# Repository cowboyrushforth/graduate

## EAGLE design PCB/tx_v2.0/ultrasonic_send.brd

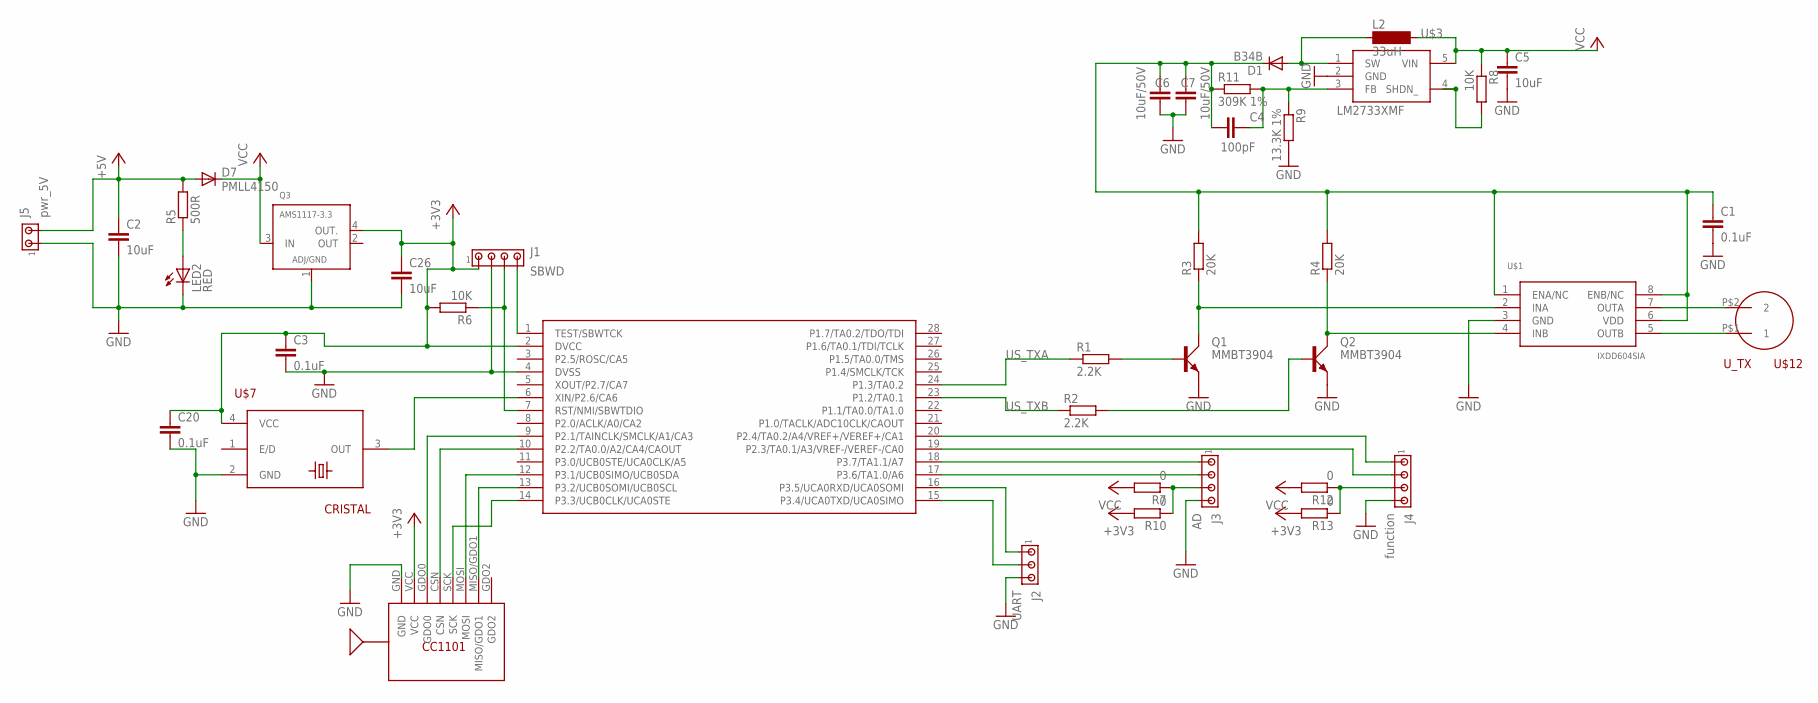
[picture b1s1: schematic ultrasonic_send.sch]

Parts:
C1, C3, C20: 0.1uF; C0805
C2, C5, C26: 10uF; C0805
C4: 100pF; C0805
C6, C7: 10uF/50V; C1210
D1: B34B; GF1
D7: PMLL4150; SOD80C
J1: SBWD; 10X04MTA
J2: UART; 10X03MTA
J3: AD; 10X04MTA
J4: function; 10X04MTA
J5: pwr_5V; 10X02MTA
L2: 33uH; MS85
LED2: RED; SML0805
Q1, Q2: MMBT3904; SOT23
Q3: AMS1117-3.3; SOT223-4
R1, R2: 2.2K; R0805
R3, R4: 20K; R0603
R5: 500R; R0603
R6, R8: 10K; R0603
R7, R10, R12, R13: 0; R0603
R9: 13.3K 1%; R0603
R11: 309K 1%; R0603
U$1: IXDD604SIA; SO8
U$2: MSP430F2112; PW_R-PDSO-G28
U$3: LM2733XMF; SOT23-DBV
U$4: CC1101
U$7: CRISTAL; CTS406
U$12: U_TX; ULTRASONIC

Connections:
+3V3: C3.1, C20.1, C26.1, J1.1, Q3.4 (OUT.), R6.2, R10.2, R13.2, U$2.2 (DVCC), U$4.VCC, U$7.4 (VCC)
+5V: C2.1, D7.A, J5.2, R5.2
GND: C1.2, C2.2, C3.2, C5.2, C6.2, C7.2, C20.2, C26.2, J1.2, J2.3, J3.4, J4.4, J5.1, LED2.C, Q1.2 (E), Q2.2 (E), Q3.1 (ADJ/GND), R9.2, U$1.3 (GND), U$2.4 (DVSS), U$3.2 (GND), U$4.GND, U$7.2 (GND)
unnamed: Q1.1 (B), R1.2
unnamed: Q2.1 (B), R2.2
unnamed: Q1.3 (C), R3.1, U$1.2 (INA)
unnamed: Q2.3 (C), R4.1, U$1.4 (INB)
unnamed: J1.4, U$2.1 (TEST/SBWTCK)
unnamed: LED2.A, R5.1
unnamed: U$2.6 (XIN/P2.6/CA6), U$7.3 (OUT)
unnamed: C1.1, C4.1, C6.1, C7.1, D1.C, R3.2, R4.2, R11.1, U$1.1 (ENA/NC), U$1.6 (VDD), U$1.8 (ENB/NC)
unnamed: J4.3, R12.1, R13.1
unnamed: J1.3, R6.1, U$2.7 (RST/NMI/SBWTDIO)
unnamed: U$2.9 (P2.1/TAINCLK/SMCLK/A1/CA3), U$4.GDO0
unnamed: U$2.10 (P2.2/TA0.0/A2/CA4/CAOUT), U$4.CSN
unnamed: U$2.12 (P3.1/UCB0SIMO/UCB0SDA), U$4.MOSI
unnamed: U$2.13 (P3.2/UCB0SOMI/UCB0SCL), U$4.MISO/GDO1
unnamed: U$2.14 (P3.3/UCB0CLK/UCA0STE), U$4.SCK
unnamed: J2.1, U$2.16 (P3.5/UCA0RXD/UCA0SOMI)
unnamed: J2.2, U$2.15 (P3.4/UCA0TXD/UCA0SIMO)
unnamed: J3.1, U$2.18 (P3.7/TA1.1/A7)
unnamed: J3.2, U$2.17 (P3.6/TA1.0/A6)
unnamed: J3.3, R7.1, R10.1
unnamed: R8.2, U$3.4 (SHDN_)
unnamed: D1.A, L2.1, U$3.1 (SW)
unnamed: C4.2, R9.1, R11.2, U$3.3 (FB)
unnamed: J4.1, U$2.20 (P2.4/TA0.2/A4/VREF+/VEREF+/CA1)
unnamed: U$1.7 (OUTA), U$12.P$2 (2)
unnamed: U$1.5 (OUTB), U$12.P$1 (1)
unnamed: J4.2, U$2.19 (P2.3/TA0.1/A3/VREF-/VEREF-/CA0)
OUT: Q3.2 (OUT)
US_TXA: R1.1, U$2.24 (P1.3/TA0.2)
US_TXB: R2.1, U$2.23 (P1.2/TA0.1)
VCC: C5.1, D7.C, L2.2, Q3.3 (IN), R7.2, R8.1, R12.2, U$3.5 (VIN)

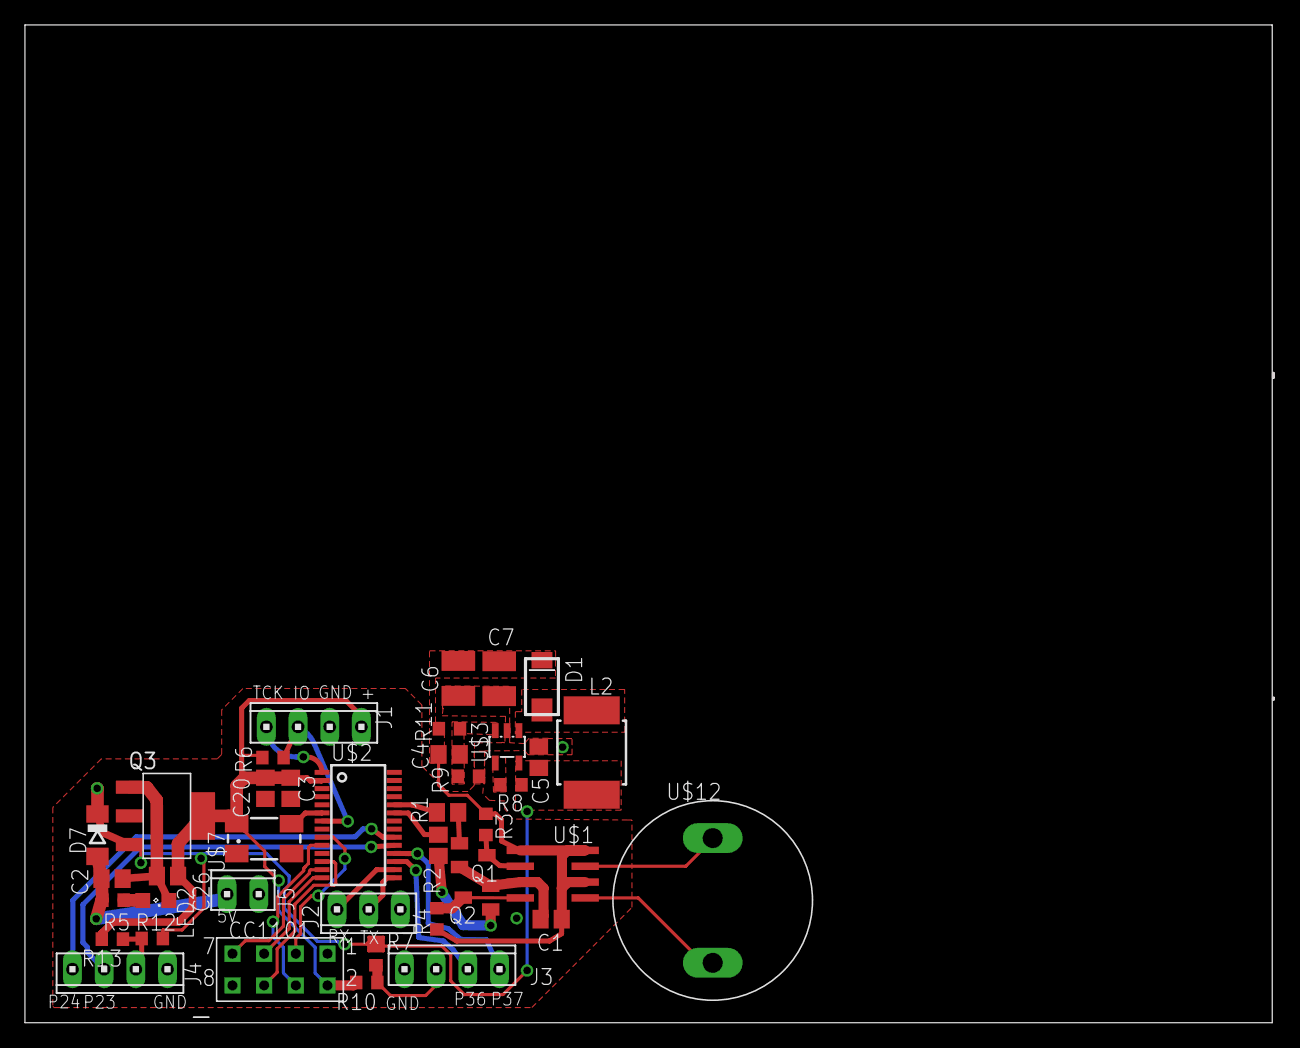
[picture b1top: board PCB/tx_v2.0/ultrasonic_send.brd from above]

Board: 2 copper layers, 100.0 x 79.7 mm, 40 parts (0 on the bottom side), 33 nets.

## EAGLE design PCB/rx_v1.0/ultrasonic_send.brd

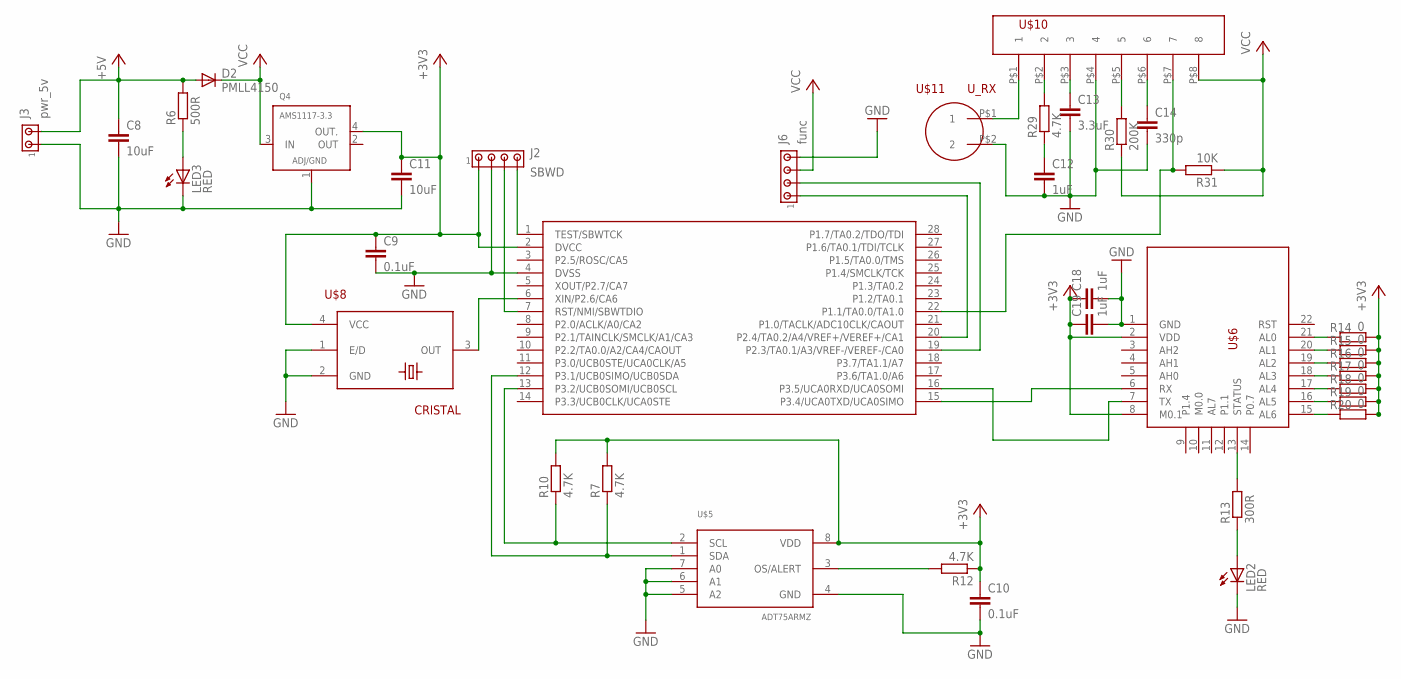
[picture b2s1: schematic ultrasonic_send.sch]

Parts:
C8, C11: 10uF; C0805
C9, C10: 0.1uF; C0805
C12, C18, C19: 1uF; C0805
C13: 3.3uF; C0805
C14: 330p; C0805
D2: PMLL4150; SOD80C
J2: SBWD; 10X04MTA
J3: pwr_5v; 10X02MTA
J6: func; 10X04MTA
LED2, LED3: RED; CHIP-LED0805
Q4: AMS1117-3.3; SOT223-4
R6: 500R; R0603
R7, R10, R12, R29: 4.7K; R0603
R13: 300R; R0603
R14, R15, R16, R17, R18, R19, R20: 0; R0603
R30: 200K; R0603
R31: 10K; R0603
U$4: MSP430F2112; PW_R-PDSO-G28
U$5: ADT75ARMZ; MSOP08
U$6: ZIGBEE
U$8: CRISTAL; CTS406
U$10: CX20106
U$11: U_RX; ULTRASONIC

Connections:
+3V3: C9.1, C10.1, C11.1, C18.1, C19.1, J2.1, Q4.4 (OUT.), R7.2, R10.2, R12.1, R14.1, R15.1, R16.1, R17.1, R18.1, R19.1, R20.1, U$4.2 (DVCC), U$5.8 (VDD), U$6.2 (VDD), U$6.8 (M0.1), U$8.4 (VCC)
+5V: C8.1, D2.A, J3.2, R6.2
GND: C8.2, C9.2, C10.2, C11.2, C12.2, C13.2, C14.2, C18.2, C19.2, J2.2, J3.1, J6.4, LED2.C, LED3.C, Q4.1 (ADJ/GND), U$4.4 (DVSS), U$5.4 (GND), U$5.5 (A2), U$5.6 (A1), U$5.7 (A0), U$6.1 (GND), U$8.1 (E/D), U$8.2 (GND), U$10.P$4 (4), U$11.P$2 (2)
unnamed: J2.4, U$4.1 (TEST/SBWTCK)
unnamed: J2.3, U$4.7 (RST/NMI/SBWTDIO)
unnamed: LED3.A, R6.1
unnamed: R12.2, U$5.3 (OS/ALERT)
unnamed: R7.1, U$4.12 (P3.1/UCB0SIMO/UCB0SDA), U$5.1 (SDA)
unnamed: R10.1, U$4.13 (P3.2/UCB0SOMI/UCB0SCL), U$5.2 (SCL)
unnamed: U$4.6 (XIN/P2.6/CA6), U$8.3 (OUT)
unnamed: U$4.16 (P3.5/UCA0RXD/UCA0SOMI), U$6.7 (TX)
unnamed: U$4.15 (P3.4/UCA0TXD/UCA0SIMO), U$6.6 (RX)
unnamed: LED2.A, R13.1
unnamed: R13.2, U$6.13 (STATUS)
unnamed: R14.2, U$6.21 (AL0)
unnamed: R15.2, U$6.20 (AL1)
unnamed: R16.2, U$6.19 (AL2)
unnamed: R17.2, U$6.18 (AL3)
unnamed: R18.2, U$6.17 (AL4)
unnamed: R19.2, U$6.16 (AL5)
unnamed: R20.2, U$6.15 (AL6)
unnamed: R29.2, U$10.P$2 (2)
unnamed: C12.1, R29.1
unnamed: U$10.P$1 (1), U$11.P$1 (1)
unnamed: C13.1, U$10.P$3 (3)
unnamed: R31.2, U$4.22 (P1.1/TA0.0/TA1.0), U$10.P$7 (7)
unnamed: R30.2, U$10.P$5 (5)
unnamed: C14.1, U$10.P$6 (6)
unnamed: J6.1, U$4.20 (P2.4/TA0.2/A4/VREF+/VEREF+/CA1)
unnamed: J6.2, U$4.19 (P2.3/TA0.1/A3/VREF-/VEREF-/CA0)
OUT: Q4.2 (OUT)
VCC: D2.C, J6.3, Q4.3 (IN), R30.1, R31.1, U$10.P$8 (8)

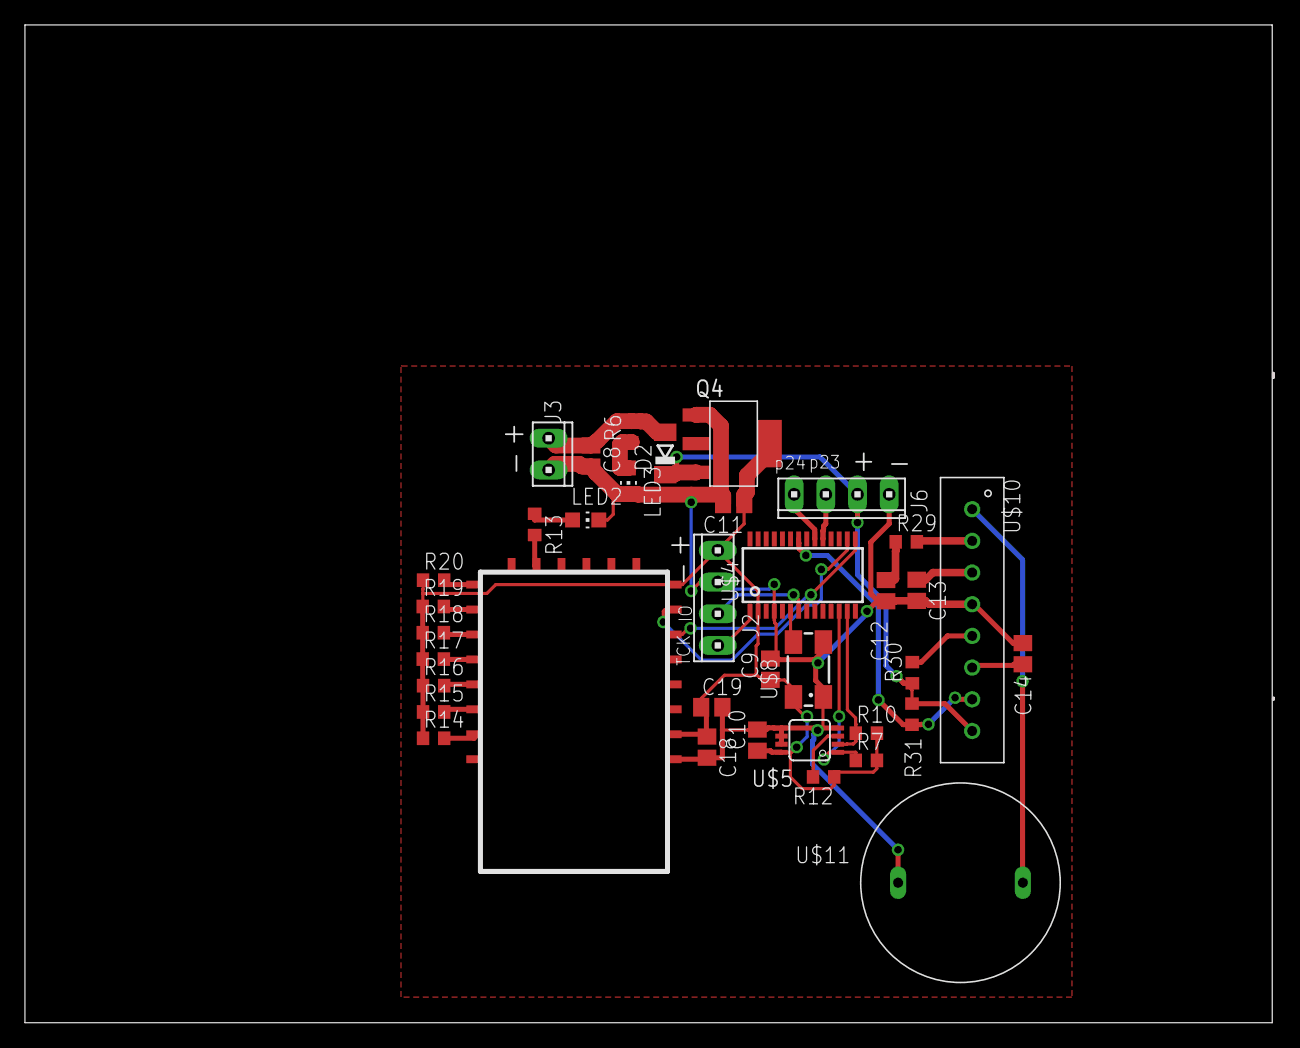
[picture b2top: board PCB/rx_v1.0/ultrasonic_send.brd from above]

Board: 2 copper layers, 100.0 x 79.7 mm, 37 parts (0 on the bottom side), 31 nets.

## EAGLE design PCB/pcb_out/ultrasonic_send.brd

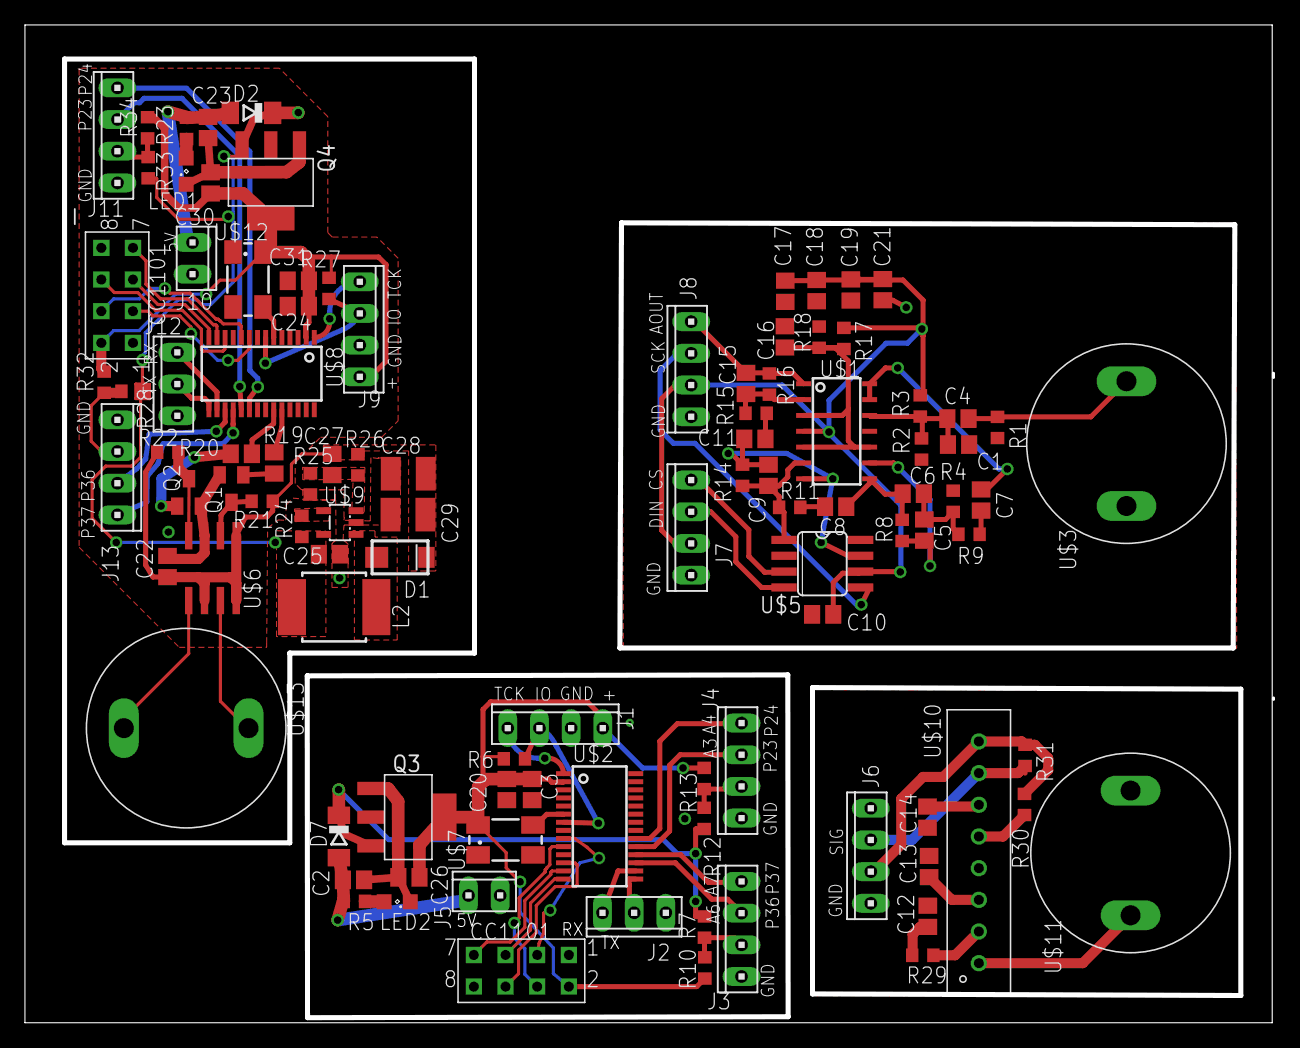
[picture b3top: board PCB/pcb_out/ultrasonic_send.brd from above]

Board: 2 copper layers, 99.8 x 79.6 mm, 102 parts (0 on the bottom side), 78 nets.

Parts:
C1, C3, C10, C16, C19, C20, C22, C24, C31: 0.1uF; C0805
C2, C23, C25, C26, C30: 10uF; C0805
C4, C7, C8, C11, C12, C17, C18: 1uF; C0805
C5: 150pF; C0805
C6: 1500pF; C0805
C9, C15, C27: 100pF; C0805
C13: 3.3uF; C0805
C14: 330p; C0805
C21: 1000pF; C0805
C28, C29: 10uF/50V; C1210
D1: B34B; GF1
D2, D7: PMLL4150; SOD80C
J1, J9: SBWD; 10X04MTA
J2, J12: UART; 10X03MTA
J3, J6, J7, J8, J13: AD; 10X04MTA
J4, J11: function; 10X04MTA
J5, J10: pwr_5V; 10X02MTA
L2: 33uH; MS85
LED1, LED2: RED; SML0805
Q1, Q2: MMBT3904; SOT23
Q3, Q4: AMS1117-3.3; SOT223-4
R1, R15: 10K 1%; R0603
R2, R3: 200K 1%; R0603
R4: 8.66K 1%; R0603
R5, R23: 500R; R0603
R6, R24, R27, R31: 10K; R0603
R7, R10, R12, R13, R28, R32, R33, R34: 0; R0603
R8: 82K 1%; R0603
R9: 953R 1%; R0603
R11: 1K 1%; R0603
R14: NC; R0603
R16, R17, R18: 100K 1%; R0603
R19, R20: 2.2K; R0805
R21, R22: 20K; R0603
R25: 13.3K 1%; R0603
R26: 309K 1%; R0603
R29: 4.7K; R0603
R30: 200K; R0603
U$1: OPA1654PW; D_R-PDSO-G14
U$2, U$8: MSP430F2112; PW_R-PDSO-G28
U$3, U$11: U_RX; ULTRASONIC
U$4, U$14: CC1101
U$5: MAX5401EKA-T; SO08
U$6: IXDD604SIA; SO8
U$7, U$12: CRISTAL; CTS406
U$9: LM2733XMF; SOT23-DBV
U$10: CX20106
U$13: U_TX; ULTRASONIC

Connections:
+3V1: C24.1, C30.1, C31.1, J9.1, Q4.4, R27.2, R32.2, R34.2, U$8.2, U$12.4, U$14.VCC
+3V3: C3.1, C20.1, C26.1, J1.1, Q3.4, R6.2, R10.2, R13.2, U$2.2, U$4.VCC, U$7.4
+5V: C2.1, D7.A, J5.2, R5.2
+5V1: C23.1, D2.A, J10.2, R23.2
AMP_OUT: C15.2, J8.1, R16.1, U$1.1
GND: C1.2, C2.2, C3.2, C10.1, C12.2, C13.2, C14.2, C16.1, C17.1, C18.1, C19.1, C20.2, C21.1, C26.2, J1.2, J2.3, J3.4, J4.4, J5.1, J6.4, J7.4, J8.4, LED2.C, Q3.1, R1.1, R2.1, R4.2, R18.2, U$1.11, U$2.4, U$3.P$1, U$4.GND, U$5.2, U$7.2, U$10.P$4, U$11.P$2
GND1: C22.2, C23.2, C24.2, C25.2, C28.2, C29.2, C30.2, C31.2, J9.2, J10.1, J11.4, J12.3, J13.4, LED1.C, Q1.2, Q2.2, Q4.1, R25.2, U$6.3, U$8.4, U$9.2, U$12.2, U$14.GND
unnamed: C4.2, R1.2, U$3.P$2
unnamed: C5.1, R8.1, U$1.9
unnamed: C1.1, C4.1, R2.2, R3.1, U$1.12
unnamed: C6.1, C8.1, R8.2, U$1.8
unnamed: J1.4, U$2.1
unnamed: LED2.A, R5.1
unnamed: U$2.6, U$7.3
unnamed: C5.2, C6.2, R4.1, R9.2
unnamed: J4.3, R12.1, R13.1
unnamed: J1.3, R6.1, U$2.7
unnamed: U$2.9, U$4.GDO0
unnamed: U$2.10, U$4.CSN
unnamed: U$2.12, U$4.MOSI
unnamed: U$2.13, U$4.MISO/GDO1
unnamed: U$2.14, U$4.SCK
unnamed: J2.1, U$2.16
unnamed: J2.2, U$2.15
unnamed: J3.1, U$2.18
unnamed: J3.2, U$2.17
unnamed: J3.3, R7.1, R10.1
unnamed: C7.1, R9.1
unnamed: C7.2, U$1.13, U$1.14
unnamed: C9.1, R11.1, R14.2, U$1.6, U$5.1
unnamed: C9.2, C11.1, R14.1, U$1.7, U$5.7
unnamed: C8.2, R11.2
unnamed: C11.2, R15.2
unnamed: C15.1, R15.1, R16.2, U$1.2
unnamed: Q1.1, R19.2
unnamed: Q2.1, R20.2
unnamed: Q1.3, R21.1, U$6.2
unnamed: Q2.3, R22.1, U$6.4
unnamed: J9.4, U$8.1
unnamed: J9.3, R27.1, U$8.7
unnamed: LED1.A, R23.1
unnamed: J11.3, R33.1, R34.1
unnamed: R24.2, U$9.4
unnamed: U$8.6, U$12.3
unnamed: D1.A, L2.1, U$9.1
unnamed: C27.2, R25.1, R26.2, U$9.3
unnamed: C22.1, C27.1, C28.1, C29.1, D1.C, R21.2, R22.2, R26.1, U$6.1, U$6.6, U$6.8
unnamed: J11.1, U$8.20
unnamed: J4.1, U$2.20
unnamed: J11.2, U$8.19
unnamed: U$8.10, U$14.CSN
unnamed: U$8.12, U$14.MOSI
unnamed: U$8.13, U$14.MISO/GDO1
unnamed: R29.2, U$10.P$2
unnamed: C12.1, R29.1
unnamed: U$10.P$1, U$11.P$1
unnamed: C13.1, U$10.P$3
unnamed: J6.2, R31.2, U$10.P$7
unnamed: R30.2, U$10.P$5
unnamed: C14.1, U$10.P$6
unnamed: U$6.7, U$13.P$2
unnamed: U$6.5, U$13.P$1
unnamed: J4.2, U$2.19
unnamed: J12.1, U$8.16
unnamed: J12.2, U$8.15
unnamed: J13.1, U$8.18
unnamed: J13.2, U$8.17
unnamed: U$8.14, U$14.SCK
unnamed: U$8.9, U$14.GDO0
unnamed: J13.3, R28.1, R32.1
SPI_CS: J7.1, U$5.3
SPI_DATA: J7.2, U$5.4
SPI_SCLK: J8.2, U$5.5
US_TXA: R19.1, U$8.24
US_TXB: R20.1, U$8.23
VCC: C10.2, C17.2, C18.2, C19.2, C21.2, D7.C, J6.3, J7.3, J8.3, Q3.3, R3.2, R7.2, R12.2, R17.1, R30.1, R31.1, U$1.4, U$5.6, U$10.P$8
VCC1: C25.1, D2.C, L2.2, Q4.3, R24.1, R28.2, R33.2, U$9.5
VREF: C16.2, R17.2, R18.1, U$1.3, U$1.5, U$1.10

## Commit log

2014-03-02 1.0version tx uart receive finished
2014-03-05 finish middle report,
2014-03-07 add ppt file of term middle
2014-03-12 finish middle term report. add time sync but not work properly
2014-03-15 start to write english middle term report
2014-03-16 finish half of english report
2014-03-16 finsihed middle term english report
2014-04-08 added CC1101 with lauchboard test.time synchronous precios is under 0.1ms finished new TX PCB with CC1101
2014-04-11 2.0 PCB finished with CC1101 and reveive modules.
